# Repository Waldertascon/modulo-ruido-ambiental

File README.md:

# Sensor de Temperatura y Humedad

Proyecto de diseno electronico — Ingenieria Electronica

## Descripcion

modulo medidor de ruido ambiental

## Equipo

| Integrante | Rol | Archivo asignado |
|---|---|---|
| AWalder tascon (lider) | Esquema raiz y gestion | Esquemagit.kicad_sch |
| rodrigo cuartas | alimentacion | Esquemagit.kicad_sch |
| Walder tascon | codigo ESP32 | codigo |
| isabella gonzalez | Pistas y PCB | Esquemagit.kicad_pcb |
| camilo manzano | Huellas y PCB | Esquemagit.kicad_pcb |

## Reglas del equipo

- Cada integrante trabaja solo en sus archivos asignados
- Avisar al grupo antes de modificar un archivo compartido
- Hacer pull antes de empezar a trabajar cada dia
- Mensajes de commit descriptivos en español

## Como abrir el proyecto

1. Instalar KiCad 8 o superior
2. Clonar el repositorio
3. Abrir sensor-temperatura.kicad_pro

## Estado

- [x] Estructura inicial del proyecto
- [ ] Esquematicos completos
- [ ] Layout PCB
- [ ] Revision DRC
- [ ] Archivos Gerber listos

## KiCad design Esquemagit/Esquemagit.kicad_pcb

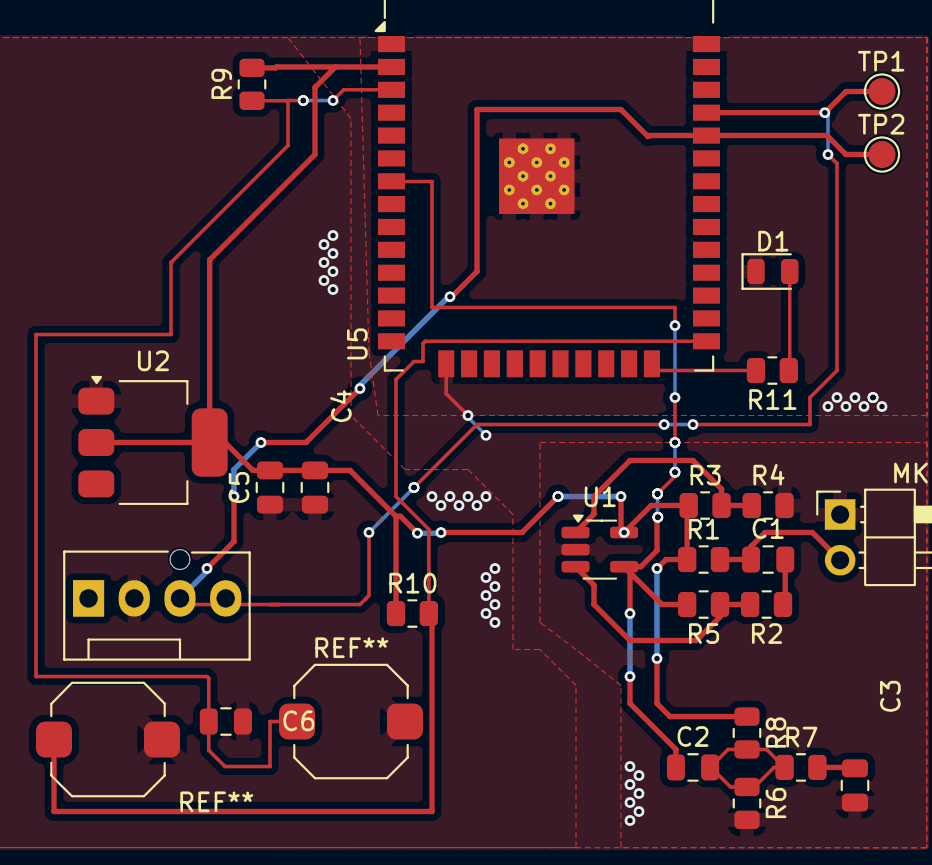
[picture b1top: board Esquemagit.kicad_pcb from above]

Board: 2 copper layers, 27 parts (0 on the bottom side), 15 nets.

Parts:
C1: 10uF; C_0805_2012Metric
C2: 1uF; C_0805_2012Metric
C3: 10nF; C_0805_2012Metric
C4, C5: 100nF; C_0805_2012Metric
C6: 100nf; C_0805_2012Metric
D1: LED; LED_0805_2012Metric
J1: Conn_01x04_Pin; FanPinHeader_1x04_P2.54mm_Vertical
MK1: Microphone_Condenser; PinHeader_1x02_P2.54mm_Horizontal
R1, R3, R4: 10K; R_0805_2012Metric
R2: 1K; R_0805_2012Metric
R5: 4.7K; R_0805_2012Metric
R6: 2.2K; R_0805_2012Metric
R7: 3.3K; R_0805_2012Metric
R8: 100K; R_0805_2012Metric
R9: 10k; R_0805_2012Metric
R10: 10; R_0805_2012Metric
R11: 47 ohm; R_0805_2012Metric
SW1, SW2: SW_Push; SW_Push_1TS009xxxx-xxxx-xxxx_6x6x5mm
TP1, TP2: TestPoint; TestPoint_Pad_D1.5mm
U1: LMV321; SOT-23-5_HandSoldering
U2: AMS1117-3.3; SOT-223-3_TabPin2
U5: ESP32-WROOM-32

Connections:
3.3V: C4.1, C5.2, R1.1, R3.1, R8.1, R9.2, R10.1, U1.5 (V+), U2.2 (VO), U5.2 (VDD)
/LED_CTRL: R11.2, U5.24 (IO2)
/RX: J1.3, TP2.1 (1_1), U5.34 (RXD0/IO3)
/TX: J1.4, TP1.1 (1_1), U5.35 (TXD0/IO1)
GND: C3.1, C4.2, C5.1, C6.2, D1.1 (K), J1.2, MK1.1 (-), R4.2, R6.2, SW1.2, SW2.2, U1.2 (V-), U2.1 (GND), U5.1 (GND), U5.15 (GND), U5.38 (GND), U5.39 (GND)
unnamed: C1.2, R2.1
unnamed: C2.2, R6.1, R7.1, R8.2
unnamed: C3.2, R7.2
unnamed: D1.2 (A), R11.1
unnamed: C1.1, MK1.2 (+), R1.2
unnamed: R2.2, R3.2, R4.1, U1.1 (+)
unnamed: R5.1, U1.3 (-)
unnamed: C6.1, R9.1, SW1.1, U5.3 (EN)
unnamed: R10.2, SW2.1, U5.25 (IO0)
salida: C2.1, R5.2, U1.4, U5.7 (IO35)

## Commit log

2026-05-01 feat: estructura completa del proyecto con todas las hojas registradas
2026-05-04 feat: fase final del esquematico
2026-05-08 feat: carpeta codigo
2026-05-08 docs: actualiza readme y gitignore
2026-05-08 feat: codigo de prueba
2026-05-08 feat inicio de pcb
2026-05-15 Se agrego huellas, se realizo avances en la etapa de amplificacion en la pcb
2026-05-17 feat: actualizaciones en el diseño del esquematico
2026-05-18 feat: actualizaciones en el diseño 2
2026-05-19 feat: huellas asignadas,botones de reset,usb-regulador,
2026-05-22 Realice ajustes de componenetes en pcb y ademas cableado de pistas
2026-05-22 agregue planos de tierra y reorganice componentes
2026-05-22 fix: se corrigieron elementos en el esquematico
2026-05-26 feat: pulsadores,usb c, huellas ,microfono digital
2026-05-27 feat: nuevo codigo(version beta)
2026-05-29 Se realizo la adicion de 5 rutas faltantes
2026-05-30 feat:nuevas rutas
2026-06-02 feat:terminado el codigo final para el proyecto
